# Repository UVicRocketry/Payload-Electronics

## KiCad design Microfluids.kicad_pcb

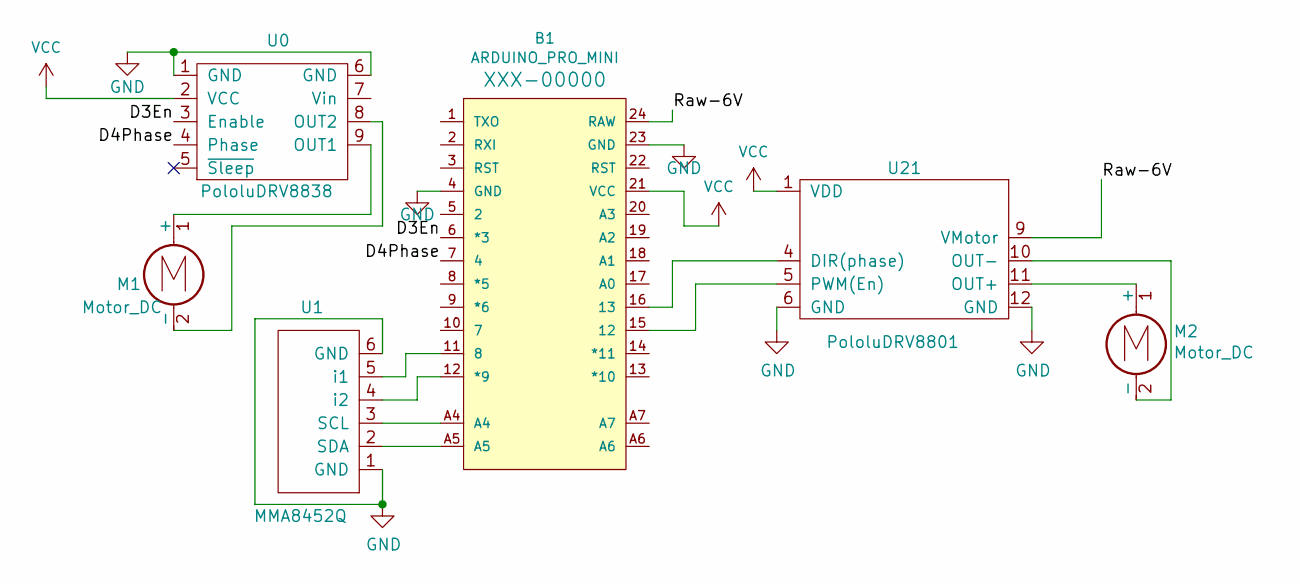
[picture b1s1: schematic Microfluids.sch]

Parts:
B1: ARDUINO_PRO_MINI
M1, M2: Motor_DC; DC-Motor
U0: PololuDRV8838; DRV8838-MotorDriv
U1: MMA8452Q; Accel - MMA8452Q
U21: PololuDRV8801; DRV8801-SpinChip

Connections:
/D3En: B1.6 (*3), U0.3 (Enable)
/D4Phase: B1.7 (4), U0.4 (Phase)
/Raw-6V: B1.24 (RAW), U21.9 (VMotor); also elsewhere on the board
GND: B1.4 (GND), B1.23 (GND), U0.1 (GND), U0.6 (GND), U1.1 (GND), U1.6 (GND), U21.6 (GND), U21.12 (GND); also elsewhere on the board
unnamed: B1.11 (8), U1.5 (i1)
unnamed: B1.12 (*9), U1.4 (i2)
unnamed: B1.15 (12), U21.5 (PWM(En))
unnamed: B1.16 (13), U21.4 (DIR(phase))
unnamed: B1.A4, U1.3 (SCL)
unnamed: B1.A5, U1.2 (SDA)
unnamed: M1.1 (+), U0.9 (OUT1)
unnamed: M1.2 (-), U0.8 (OUT2)
unnamed: M2.1 (+), U21.11 (OUT+)
unnamed: M2.2 (-), U21.10 (OUT-)
VCC: B1.21 (VCC), U0.2 (VCC), U21.1 (VDD)

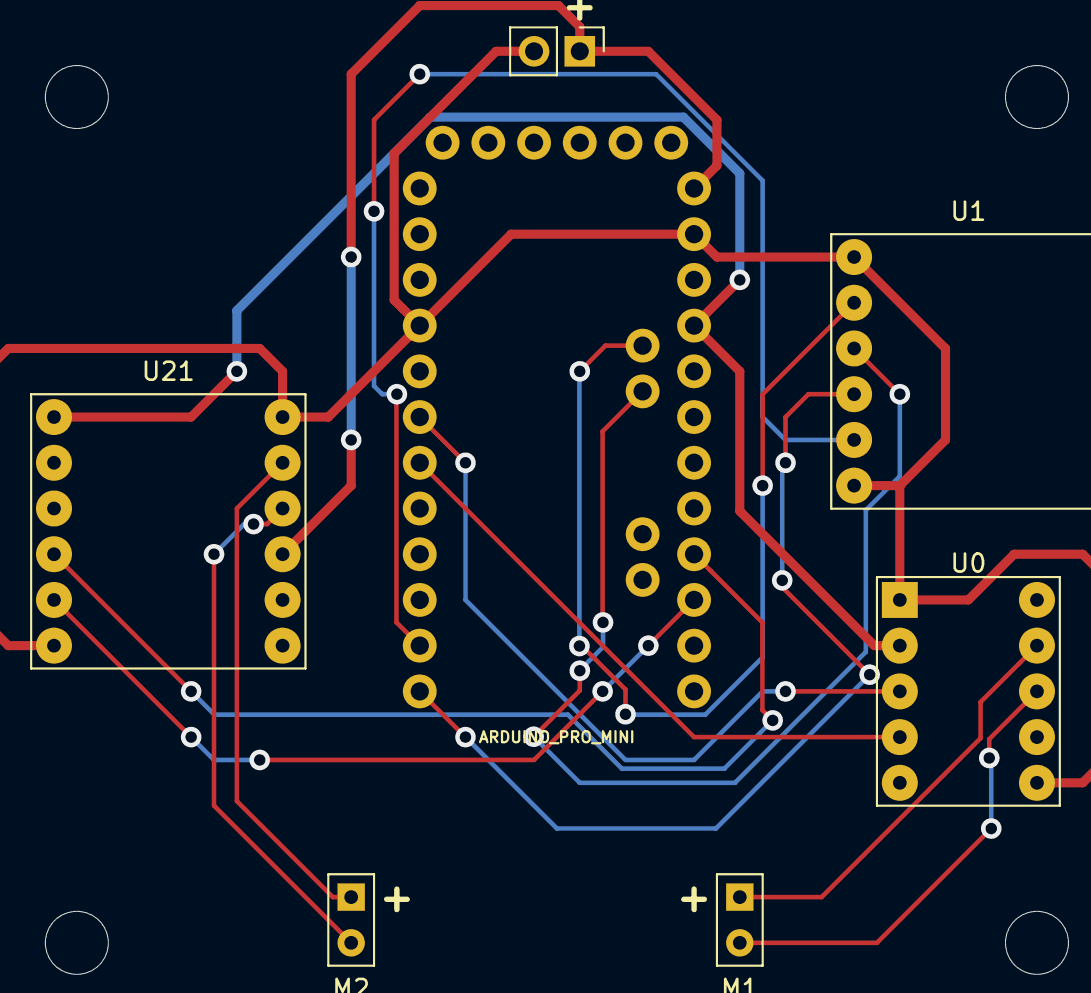
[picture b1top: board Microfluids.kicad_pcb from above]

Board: 2 copper layers, 7 parts (0 on the bottom side), 15 nets.

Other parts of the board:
R: PinHeader_1x02_P2.54mm_Vertical

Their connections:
/Raw-6V: R.1; also elsewhere on the board
GND: R.2; also elsewhere on the board

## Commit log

2020-03-19 initial altimeter
2020-03-28 Accelerometer code
2020-08-15 Payload Circuit Diagram
